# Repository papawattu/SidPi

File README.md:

SidPi v1
==========

A Raspberry Pi driver for the MOS 6581 SID chip used in the Commodore 64.  There are three components to the driver, a kernel driver that uses the same protocol as the hardsid driver.  A network listener that implements the netsid protocol used by ACID64, and a proxy is required to forward requests from a PC running ACID64 to a Raspberry Pi where the listener is running.

The GPIO connections and schematic can be found in the schematic folder which includes a simple implementation of the hardware required.  Any implementation of this design is at your own risk !  Do not blame me for any blown up Pi's or SID's or anything for that matter.

Build instructions to follow as I'm trying to automate it all, however if you wish to know before that then feel free to contact me at papawattu@gmail.com.

1) module -Raspberry Pi Kernel Module

You'll need to have the RPi kernel source headers which match your kernel version and then create a softlink /lib/modules/<kernelversion>/build to the root of the kernel source.  

Perform a make in the kernel source dir to make the module.

Then just do an insmod sidpi.ko and a dmesg to see if the driver has loaded.  You will also need to mknod /dev/sid0 c 248 0 to create the device.  At that point you should be able to use sidplay2 with the --hardsid parameter to play some rockin Sid tunes.

14/2/2016
The Module is still very much under development is broken at the moment.

2) sidpiserver - Network listener for ACID 64 - listens by default on port 6581

To build the server in the sidpiserver src directory

gcc -pthread -o sidpiserver sidpiserver.c sidpithread.c rpi.c fifo.c

To setup a proxy to forward the ACID64 traffic you can use (on Windows)..

netsh interface portproxy add v4tov4 listenport=6581 listenaddress=127.0.0.1 connectport=6581 connectaddress=<IP of your PI>

You can order the PCB from here https://oshpark.com/shared_projects/vRw7mWuD

More to come soon!

UPDATE 14/2/16

Changes to support Pi2 and some timing fixes.

UPDATE 27/4/15

The driver does not work with RP2 - Looking into this now

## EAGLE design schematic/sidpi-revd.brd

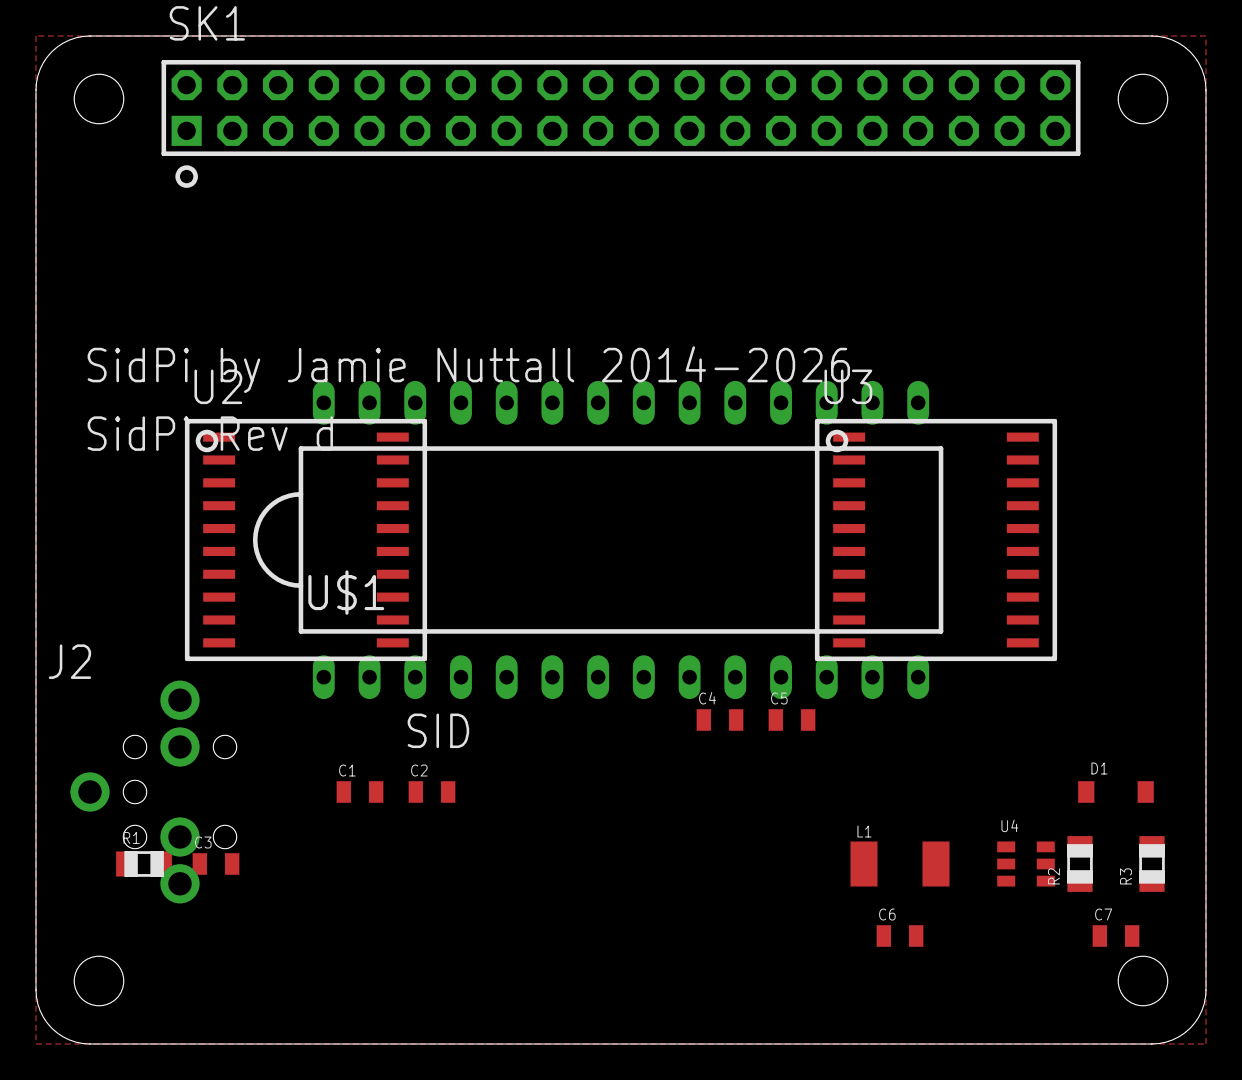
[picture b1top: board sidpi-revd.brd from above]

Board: 2 copper layers, 65.0 x 56.0 mm, 18 parts (0 on the bottom side), 28 nets, no tracks yet.

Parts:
C1, C2: 2.2nF; 0805
C3: 1µF; 0805
C4, C5: 100nF; 0805
C6, C7: 22µF; 0805
D1: SS14; SOD-123
J2: AUDIO-JACK-KIT
L1: 22µH; IND-5X5
R1: 1K; R0805
R2: 150K; R0805
R3: 7.87K; R0805
SK1: GPIO-CONNECTOR-40
U2, U3: SOIC20W
U4: SOT-23-6
U$1: DIL28-6

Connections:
+3V3: SK1.1, SK1.17, U2.1, U3.1
GND: C4.2, C5.2, C6.2, C7.2, J2.SLEEVE, R1.1, R3.1, SK1.6, SK1.9, SK1.14, SK1.20, SK1.25, U2.10, U2.19, U3.10, U3.19, U4.2, U$1.7, U$1.14
unnamed: SK1.5, U3.7, U3.13, U$1.8
unnamed: SK1.12, U3.5, U3.15, U$1.12
unnamed: C1.1, U$1.1
unnamed: SK1.8, U3.6, U3.14, U$1.13
unnamed: SK1.10, U2.9, U2.11, U$1.22
unnamed: C2.1, U$1.3
unnamed: SK1.11, U2.8, U2.12, U$1.21
unnamed: C3.2, J2.RING, J2.TIP
unnamed: SK1.7, U3.8, U3.12, U$1.6
unnamed: SK1.13, U2.7, U2.13, U$1.20
unnamed: SK1.15, U2.6, U2.14, U$1.19
unnamed: SK1.18, U2.5, U2.15, U$1.18
unnamed: SK1.19, U2.4, U2.16, U$1.17
unnamed: SK1.21, U2.3, U2.17, U$1.16
unnamed: C2.2, U$1.4
unnamed: C1.2, U$1.2
unnamed: SK1.23, U2.2, U2.18, U$1.15
unnamed: SK1.16, U3.4, U3.16, U$1.11
unnamed: C3.1, R1.2, U$1.27
unnamed: SK1.24, U3.2, U3.18, U$1.9
unnamed: SK1.22, U3.3, U3.17, U$1.10
unnamed: SK1.3, U3.9, U3.11, U$1.5
unnamed: D1.A, L1.2, U4.1
unnamed: R2.1, R3.2, U4.3
VCC: C4.1, C6.1, L1.1, SK1.2, U2.20, U3.20, U4.4, U4.5, U$1.25
VDD: C5.1, C7.1, D1.C, R2.2, U$1.28

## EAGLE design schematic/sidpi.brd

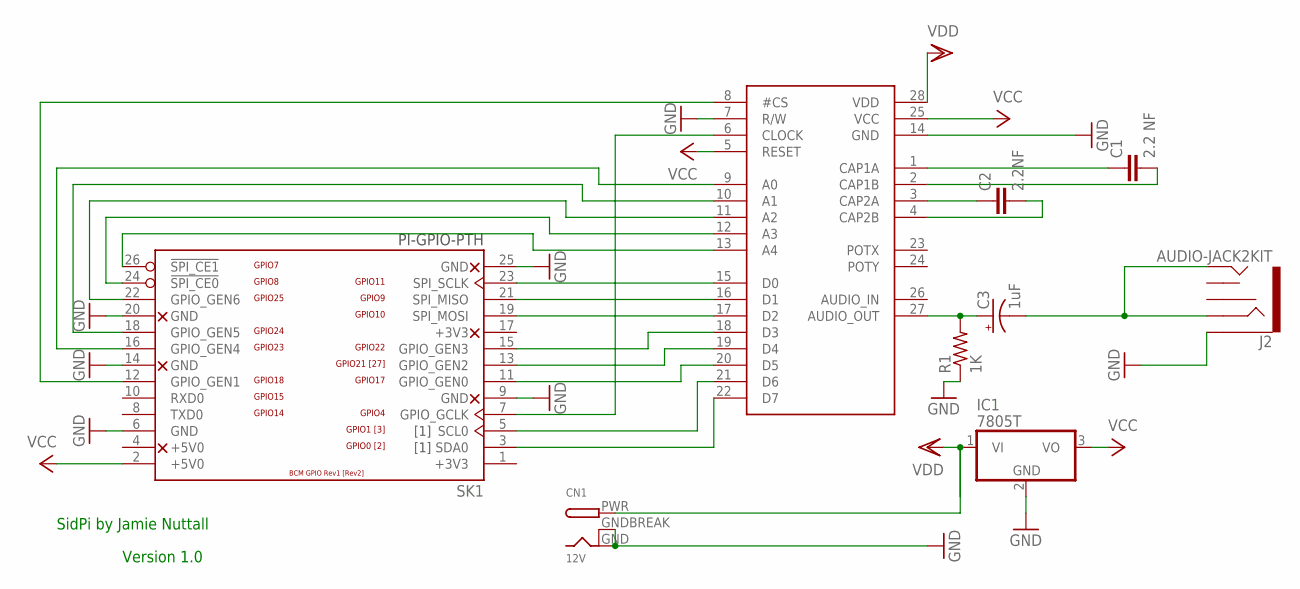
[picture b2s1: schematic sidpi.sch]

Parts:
C1: 2.2 NF; CAP-PTH-SMALL2
C2: 2.2NF; CAP-PTH-SMALL2
C3: 1uF; E1,8-4
CN1: 12V; DCJACK_2MM_PTH
IC1: 7805T; TO220H; MPN BA17805T
J2: AUDIO-JACK2KIT; AUDIO-JACK-KIT
R1: 1K; 0309/10
SK1: PI-GPIO-PTH; GPIO-CONNECTOR
U$1: 6581; DIL28-6

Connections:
+3V3: SK1.1 (+3V3)
GND: CN1.GND, CN1.GNDBREAK, IC1.2 (GND), J2.SLEEVE, R1.1, SK1.6 (GND), SK1.9 (GND), SK1.14 (GND), SK1.20 (GND), SK1.25 (GND), U$1.7 (R/W), U$1.14 (GND)
unnamed: SK1.12 (GPIO_GEN1), U$1.8 (#CS)
unnamed: SK1.24 (!SPI_CE0), U$1.12 (A3)
unnamed: C1.1, U$1.1 (CAP1A)
unnamed: SK1.26 (!SPI_CE1), U$1.13 (A4)
unnamed: SK1.3 (SDA0), U$1.22 (D7)
unnamed: C2.1, U$1.3 (CAP2A)
unnamed: SK1.5 (SCL0), U$1.21 (D6)
unnamed: C3.-, J2.RING, J2.TIP
unnamed: SK1.7 (GPIO_GCLK), U$1.6 (CLOCK)
unnamed: SK1.11 (GPIO_GEN0), U$1.20 (D5)
unnamed: SK1.13 (GPIO_GEN2), U$1.19 (D4)
unnamed: SK1.15 (GPIO_GEN3), U$1.18 (D3)
unnamed: SK1.19 (SPI_MOSI), U$1.17 (D2)
unnamed: SK1.21 (SPI_MISO), U$1.16 (D1)
unnamed: C2.2, U$1.4 (CAP2B)
unnamed: C1.2, U$1.2 (CAP1B)
unnamed: SK1.23 (SPI_SCLK), U$1.15 (D0)
unnamed: SK1.22 (GPIO_GEN6), U$1.11 (A2)
unnamed: C3.+, R1.2, U$1.27 (AUDIO_OUT)
unnamed: SK1.16 (GPIO_GEN4), U$1.9 (A0)
unnamed: SK1.18 (GPIO_GEN5), U$1.10 (A1)
VCC: IC1.3 (VO), SK1.2 (+5V0), U$1.5 (RESET), U$1.25 (VCC)
VDD: CN1.PWR, IC1.1 (VI), U$1.28 (VDD)

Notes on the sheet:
SidPi by Jamie Nuttall
Version 1.0

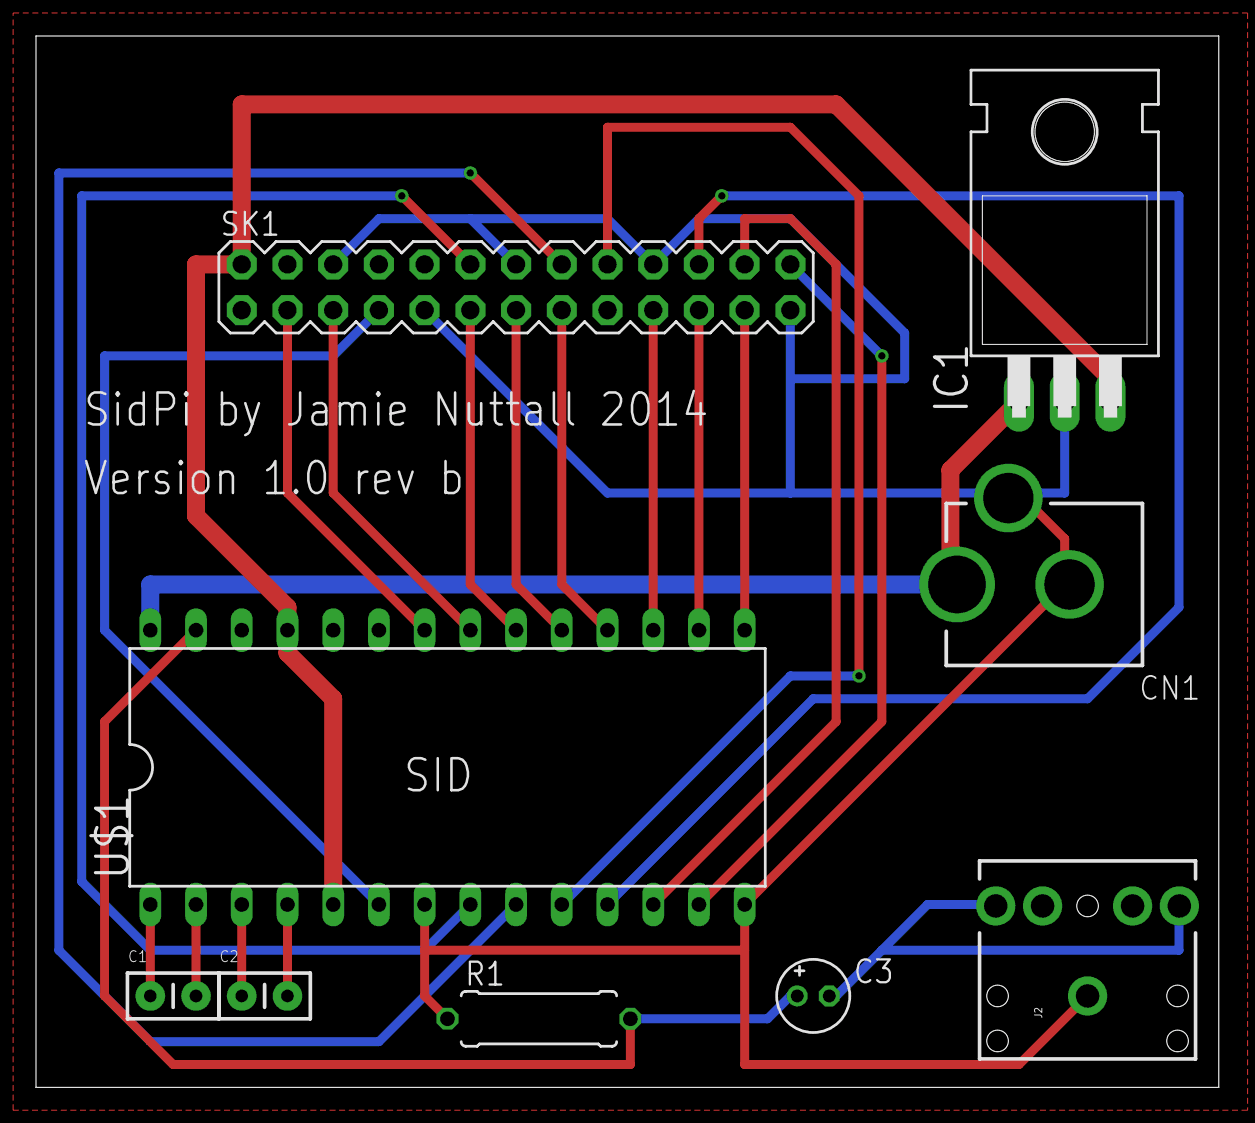
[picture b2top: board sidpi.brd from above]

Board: 2 copper layers, 65.7 x 58.4 mm, 9 parts (0 on the bottom side), 24 nets.

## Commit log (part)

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2014-04-15 Update sidpithread.c
    Added more robust delay.
2014-04-16 Update sidpithread.h
    reduced buffer size
2014-04-23 Added schematic
2014-04-23 Deleted object files
2014-04-24 First attempt at a tidy up
    Moved files into separate folders and added repeater code from old SidPi
    project.
2014-04-24 More tidy up
2014-04-24 Created Readme
2014-06-11 moved pins for new PCB layout
2014-06-11 fixed one incorrect pin
2014-06-11 Changed to new pin layout to match v1.1 schmatic
2014-06-11 CS GPIO pin was wrong now fixed
2014-06-11 Updated schematic
2014-06-11 changed delay to usleep
2014-06-14 Update README.md
    Added instructions for stone and corrected the gcc server compile instructions
2014-06-15 timing fix attempt
2014-06-17 removed delay from writesid and moved CS low to above addr line set
2014-07-14 Timing issues
2014-07-14 fixed compile error
2014-07-23 fixed schematic
2014-07-23 delay issues
2014-07-23 added underbuffer protection
2014-07-23 changes write delay from 100us to u500us
2014-07-23 changes thread priority to 40
2014-07-23 Added getmaxpriority and lowered CS delay t0 600us
2014-07-23 wrong sys call for priority
2014-07-23 added missing header
2014-08-10 removed get max priority
2014-08-11 added new serialsid
2014-08-11 fixed compilation issues
2014-08-11 created serialsid header file
2014-08-11 added test harness for serialsid
2014-08-11 set pin 4 to clock
2014-08-11 clock fix
2014-08-11 fixed CLK setup
2014-08-11 compile error
2014-08-12 fixed pin layouts
2014-09-04 Started async timer conversion
2014-09-09 Refactored the timer to use RT timer
2014-09-09 converted sidserver to use module added some (broken) reset logic
2014-09-10 Update sidpithread.c
    Added a semaphore for the reset
2014-09-11 Cleaned up code and fixed reset.
2014-09-12 changed the reset to restart the thread instead
2014-09-14 Enabled reset and flush IOctls
2014-09-23 Added serial SID interface parameter changes,but not yet implemented writeSidSer() function.
2015-04-27 Update sidpithread.h
    Added new entry to support Pi2
2015-04-27 Update sidpi.c
    Added Pi2 module parameter
2015-04-27 Update sidpithread.c
    added Pi2 support
2015-04-27 Update sidpithread.h
    added support for pi2
2016-02-14 Added some thread safety checks
2016-02-14 Added new fifo code
2016-02-14 I forgot what year it is
2016-02-14 Fixed bug spiining up two threads
2016-02-14 Fixed timing
2016-02-14 Reduced the buffer
2016-03-11 Major refactor to module.
2016-03-11 Fix .gitignore.
2016-04-29 Added player
2016-04-29 Changed player to select sid 0
2016-04-29 Removed some dead code, and implemented sid delay
2016-05-02 Added speed fix to module
2016-05-02 updated gitignore
2016-05-02 Fixed some compiler warnings.
2016-05-02 Fixed issue with parenthses
2016-05-02 Few tidy ups
2016-05-02 update to readme
2016-05-03 Updates to gitignore
2016-05-03 Update to player code to make more moduler
2016-05-03 Added deprecated warning on the sid proxy
2016-05-09 Worked started on restful web interface running on node.
2016-05-09 more code added to restful service
2026-04-16 Add Rev d schematic redesign with level shifters, boost converter, and SMD components
    - Preserve original Rev b schematic/board as sidpi-revb.sch/brd
    - Add Rev d schematic (sidpi-revd.sch) with 74HCT245 level shifters,
    MT3608 5V-to-12V boost converter, SMD passives, 40-pin GPIO header
    - Add Rev d board layout (sidpi-revd.brd) with HAT-compliant 65x56mm
    outline, mounting holes, and component placements
    - Add manufacturing BOM and CPL files
2026-04-16 Add Rev d schematic renders (PDF and PNG)
2026-04-16 Add routing strategy guide and DRC rules file
2026-04-16 Add KiCad project wrapper file

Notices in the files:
parts and their libraries:
SparkFun-Capacitors: Licensing: Creative Commons ShareAlike 4.0 International - https://creativecommons.org/licenses/by-sa/4.0
